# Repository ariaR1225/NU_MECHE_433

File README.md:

# NU_MECHE_433
MECHE_433: Advanced Mechatronics @ Northwestern SP 2023

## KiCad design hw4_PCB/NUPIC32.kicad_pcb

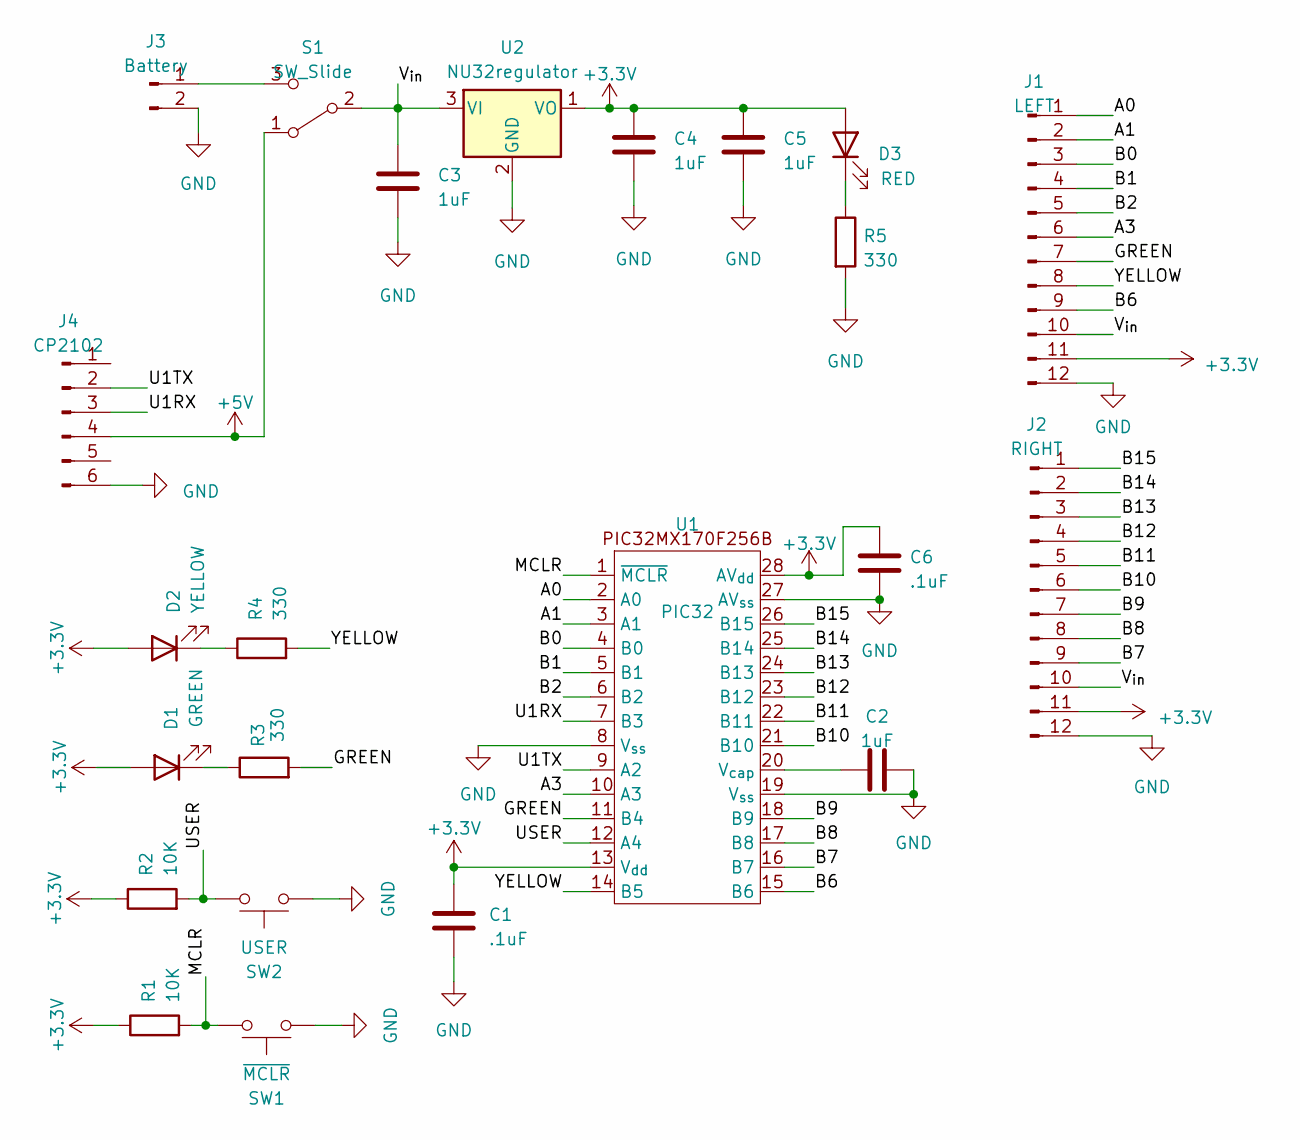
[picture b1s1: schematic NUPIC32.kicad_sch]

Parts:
C1, C6: .1uF; C_Disc_D3.4mm_W2.1mm_P2.50mm
C2, C3, C4, C5: 1uF; C_Disc_D3.4mm_W2.1mm_P2.50mm
D1: GREEN; LED_D3.0mm
D2: YELLOW; LED_D3.0mm
D3: RED; LED_D3.0mm
J1: LEFT; PinSocket_1x12_P2.54mm_Vertical
J2: RIGHT; PinSocket_1x12_P2.54mm_Vertical
J3: Battery; PinSocket_1x02_P2.54mm_Vertical
J4: CP2102; PinSocket_1x06_P2.54mm_Vertical
R1, R2: 10K; R_Axial_DIN0207_L6.3mm_D2.5mm_P7.62mm_Horizontal
R3, R4, R5: 330; R_Axial_DIN0207_L6.3mm_D2.5mm_P7.62mm_Horizontal
S1: SW_Slide; slidesw
SW1: ~{MCLR}; PB
SW2: USER; PB
U1: PIC32; DIP-28_W7.62mm_Socket
U2: NU32regulator; TO-92L_Inline

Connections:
+3.3V: C1.1, C4.1, C5.1, C6.2, D1.2 (A), D2.2 (A), D3.2 (A), J1.11, J2.11, R1.1, R2.1, U1.13 (V_{dd}), U1.28 (AV_{dd}), U2.1 (VO)
+5V: J4.4, S1.1 (A)
/A0: J1.1, U1.2 (A0)
/A1: J1.2, U1.3 (A1)
/A3: J1.6, U1.10 (A3)
/B0: J1.3, U1.4 (B0)
/B1: J1.4, U1.5 (B1)
/B2: J1.5, U1.6 (B2)
/B6: J1.9, U1.15 (B6)
/B7: J2.9, U1.16 (B7)
/B8: J2.8, U1.17 (B8)
/B9: J2.7, U1.18 (B9)
/B10: J2.6, U1.21 (B10)
/B11: J2.5, U1.22 (B11)
/B12: J2.4, U1.23 (B12)
/B13: J2.3, U1.24 (B13)
/B14: J2.2, U1.25 (B14)
/B15: J2.1, U1.26 (B15)
/GREEN: J1.7, R3.2, U1.11 (B4)
/MCLR: R1.2, SW1.2, U1.1 (~MCLR)
/U1RX: J4.3, U1.7 (B3)
/U1TX: J4.2, U1.9 (A2)
/USER: R2.2, SW2.2, U1.12 (A4)
/V_{in}: C3.1, J1.10, J2.10, S1.2 (B), U2.3 (VI)
/YELLOW: J1.8, R4.2, U1.14 (B5)
GND: C1.2, C2.1, C3.2, C4.2, C5.2, C6.1, J1.12, J2.12, J3.2, J4.6, R5.2, SW1.1, SW2.1, U1.8 (V_{ss}), U1.19 (V_{ss}), U1.27 (AV_{ss}), U2.2 (GND)
unnamed: D1.1 (K), R3.1
unnamed: D2.1 (K), R4.1
unnamed: D3.1 (K), R5.1
unnamed: J3.1, S1.3 (C)
unnamed: C2.2, U1.20 (V_{cap})

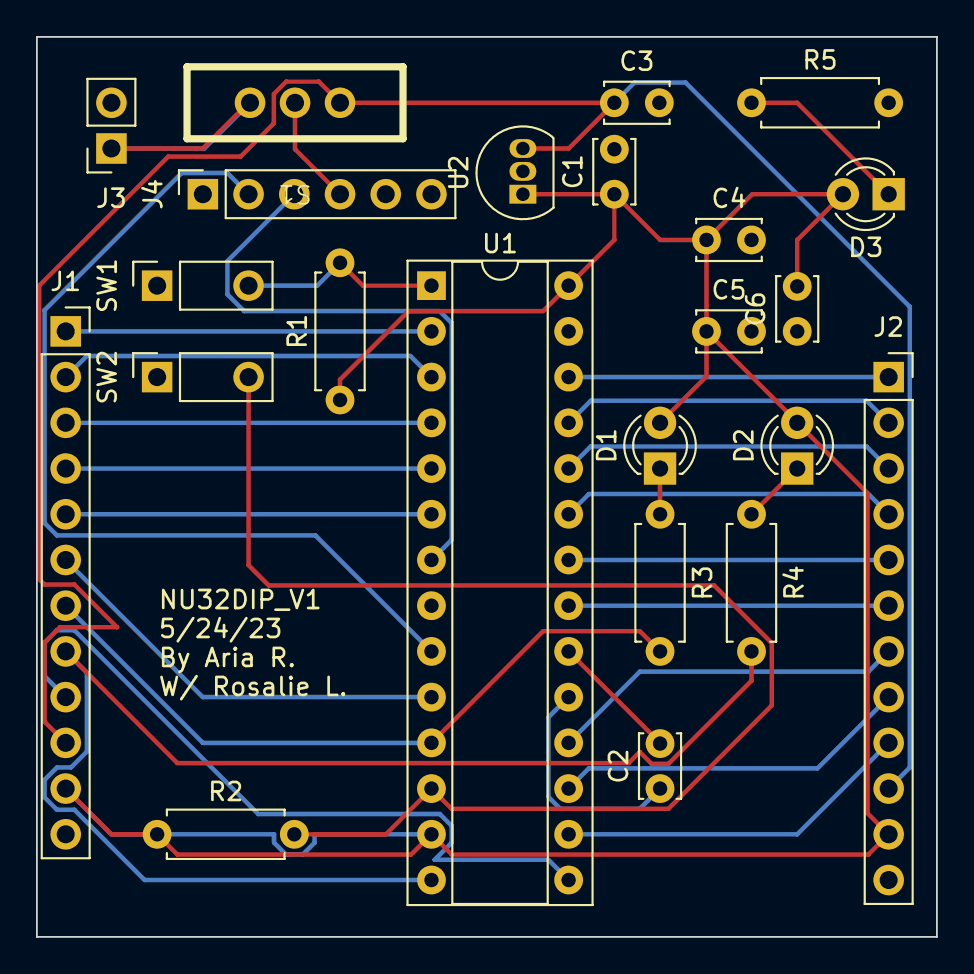
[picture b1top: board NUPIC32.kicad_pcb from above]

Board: 2 copper layers, 50.0 x 50.0 mm, 23 parts (0 on the bottom side), 31 nets.

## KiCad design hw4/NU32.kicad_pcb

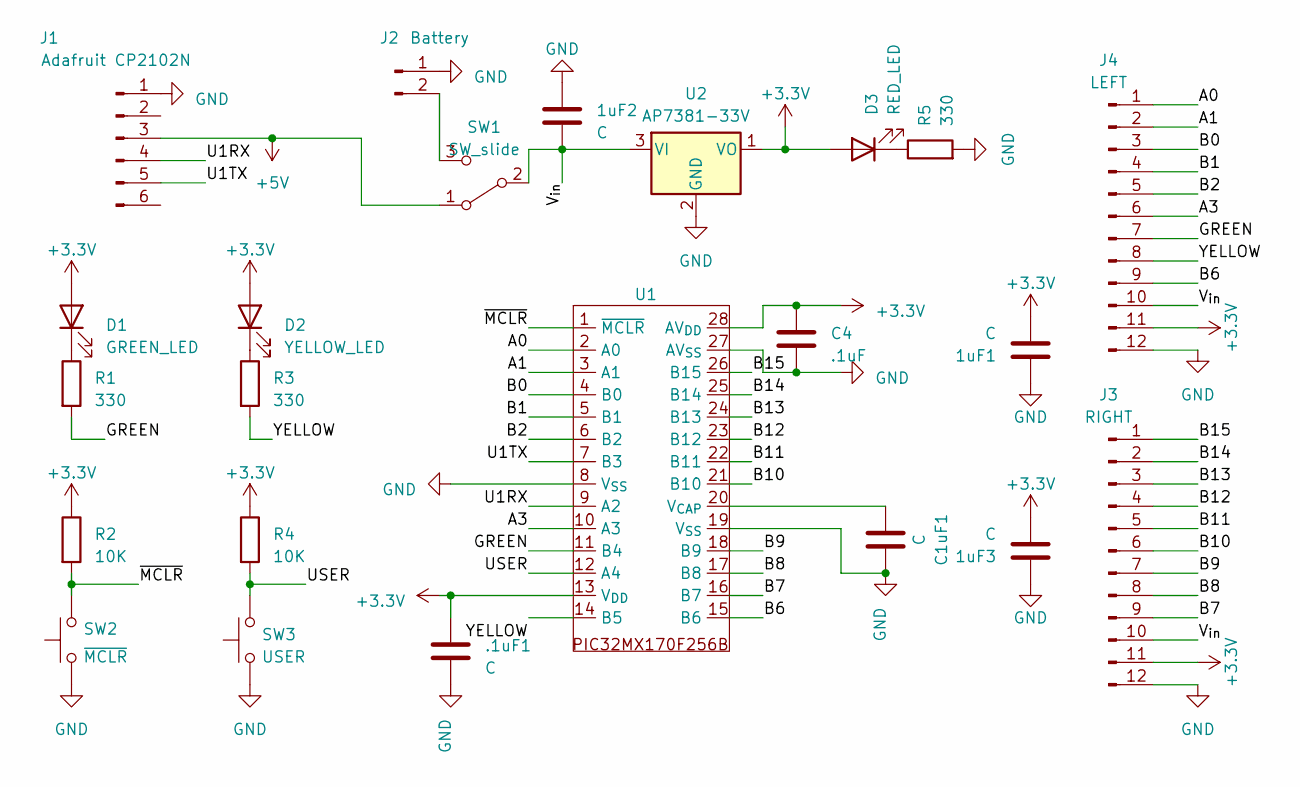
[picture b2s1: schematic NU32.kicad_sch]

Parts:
1uF1, 1uF2, 1uF3, .1uF1: C; C_Disc_D5.1mm_W3.2mm_P5.00mm
C1uF1: C; C_Disc_D5.1mm_W3.2mm_P5.00mm
C4: .1uF; C_Disc_D5.1mm_W3.2mm_P5.00mm
D1: GREEN_LED; LED_D3.0mm
D2: YELLOW_LED; LED_D3.0mm
D3: RED_LED; LED_D3.0mm
J1: Adafruit CP2102N; PinSocket_1x06_P2.54mm_Vertical
J2: Battery; PinSocket_1x02_P2.54mm_Vertical
J3: RIGHT; PinSocket_1x12_P2.54mm_Vertical
J4: LEFT; PinSocket_1x12_P2.54mm_Vertical
R1, R3, R5: 330; R_Axial_DIN0207_L6.3mm_D2.5mm_P7.62mm_Horizontal
R2, R4: 10K; R_Axial_DIN0207_L6.3mm_D2.5mm_P7.62mm_Horizontal
SW1: SW_slide; SlideSW
SW2: ~{MCLR}; PBSwitch
SW3: USER; PBSwitch
U1: DIP-28_W7.62mm_Socket
U2: AP7381-33V; TO-92_Inline

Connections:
+3.3V: 1uF1.1, 1uF3.1, .1uF1.1, C4.1, D1.2 (A), D2.2 (A), D3.2 (A), J3.11, J4.11, R2.1, R4.1, U1.13 (V_{DD}), U1.28 (AV_{DD}), U2.1 (VO)
+5V: J1.3, SW1.1 (A)
/A0: J4.1, U1.2 (A0)
/A1: J4.2, U1.3 (A1)
/A3: J4.6, U1.10 (A3)
/B0: J4.3, U1.4 (B0)
/B1: J4.4, U1.5 (B1)
/B2: J4.5, U1.6 (B2)
/B6: J4.9, U1.15 (B6)
/B7: J3.9, U1.16 (B7)
/B8: J3.8, U1.17 (B8)
/B9: J3.7, U1.18 (B9)
/B10: J3.6, U1.21 (B10)
/B11: J3.5, U1.22 (B11)
/B12: J3.4, U1.23 (B12)
/B13: J3.3, U1.24 (B13)
/B14: J3.2, U1.25 (B14)
/B15: J3.1, U1.26 (B15)
/GREEN: J4.7, R1.2, U1.11 (B4)
/U1RX: J1.4, U1.9 (A2)
/U1TX: J1.5, U1.7 (B3)
/USER: R4.2, SW3.2, U1.12 (A4)
/V_{in}: 1uF2.1, J3.10, J4.10, SW1.2 (B), U2.3 (VI)
/YELLOW: J4.8, R3.2
/~MCLR: R2.2, SW2.2, U1.1 (~MCLR)
GND: 1uF1.2, 1uF2.2, 1uF3.2, .1uF1.2, C1uF1.2, C4.2, J1.1, J2.1, J3.12, J4.12, R5.2, SW2.1, SW3.1, U1.8 (V_{SS}), U1.19 (V_{SS}), U1.27 (AV_{SS}), U2.2 (GND)
unnamed: D1.1 (K), R1.1
unnamed: D2.1 (K), R3.1
unnamed: D3.1 (K), R5.1
unnamed: J2.2, SW1.3 (C)
unnamed: C1uF1.1, U1.20 (V_{CAP})

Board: 2 copper layers, 23 parts (0 on the bottom side), 31 nets, no tracks yet.

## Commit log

2023-03-28 Create KeyLimePie.md
    created recipe
2023-05-26 update hw10
2023-06-05 15/16 hw done
